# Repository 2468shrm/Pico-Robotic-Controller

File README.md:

# Pico-Robotic-Controller

A carrier board for a Raspberry Pi Pico (W) for use in FRC robotics. Similar
to the XRP board.

## Disclaimer / Warning

This is an experimental device. Not all interfaces have been fully validated
for proper function. Use at your own risk.

## Introduction (Motivation)

You may assume that this board is indended to compete with the XRP product
from WPI, other developers, and SparkFun. __It is not__. The XRP board is
awesome and I'll likely end up acquiring one (or two) for myself. I have
been working on lo w-cost, roboRIO-like carrier boards for FRC for a couple
of years.

Why create a carrier board like the roboRIO? To enable a lower-cost
prototyping solution. This solution makes it less risky to a costly
than using a roboRIO solution. Breaking a roboRIO means costly replacement
that is sometimes hard to replace. One goal was to provide as many
similar interfaces as possible but cost 25% the budget.

Things I didn't need to do with my use model: support LabVIEW despite being
a team who lives and breaths LabVIEW. I did want to support rapid prototyping
and so exploring circuitpython was a goal; particularly because of the
library support for the STEMMA QT/Qwiic based sensors available from
Adafruit.

## Board Images

## Board Features

The carrier board has the following interfaces and features.

- RaspberryPi Pico W board
  - Does the thinking
  - Provides WiFi and/or Bluetooth
  - Socketed for replacemnt if needed
- Adafruit Picobell CAN board (optional)
  - Provides CAN connectivity for integration into FRC robots allowing CAN-connected applications (e.g. smart sensors)
- Adafruit Ethernet Featherwing board (optional)
  - Provides Ethernet connectivity for integration into FRC robots allowing Ethernet connected applications (e.g. smart sensors)
- Power
  - 12V Battery input provides main board supply
    - 5V regulator module, OR
    - A connection to external 5V regulator (using WAGO 250-202) connector if the 5V supply current requirements are higher than the module can provide
  - Servo/PWM interface independently powered by an external source
    - Due to the potential need for different voltage and higher current
    - Not needed if connecting to external motor controllers (REV, CTRE, etc.)
- Four (4) STEMMA QT/Qwiic connections provided through a 4-port I2C switch run off the Pico W I2C 1 interface
- Eight (8) Servo PWM interfaces and an additional 8 PWM signals generated by a 16-channel generator connected to the Pico W I2C 0 interface
 - The Servo PWM interace has its own power input; for increased voltage or current for high-torque servo motors
- Two (2) analog input (ADC) ports, 3V maximum
- Eight (8) digital I/O ports, divided into 2 4-pin groups
  - Uses the roboRIO DIO 3-pin interface
  - Each group provides jumper-selectable power (5V or 3.3V)
  - Pico inputs are 3.3V only (maximum) input, with level shifting based on the group's selected power
  - All DIOs have LEDs to indicate logic level (Dark is LOW, Illuminated is HIGH)
- One NEOPIXEL interface for providing visual sensor status or communication
- One on-board single-pixel NEOPIXEL for board status

## Comparison to XRP Board

The XRP board has some significant philospohical and design choices and features.

- XRP was designed with the intent of learning robotics on a small platform, using the WPILib framework
- Includes four motor controllers (1.5A each) integrated on the PCB
- Has a gyro and accelerometer integrated on the PCB
- The connectors are six-position JST (vertical) that integrates digital I/Os for encoders in addition to the M+ and M- motor signals (i.e. not a sensor standard like Qwiic or STEMMA QT)

The PRC does not include any motor controllers on the board. However, it
does provide a 2x5 pin connector and a dedicated PWM generator (I2C bus 0,
address 0x41). The intent is to provide a board with 4 12V, 3.3 A motor
controllers using a separate/dedicated battery input. Providing the capability
to drive four H-Bridges allows for demonstration chassis (skid steer or
Meccanum). This allows replaceable solutions as well as future upgrades for
higher current. Moreover, the PWM / Servo connections allow for use of
a conventional FRC PWM-controlled motor controller.

The PRC provides four STEMMA QT / Qwiic connectors in lieu of a specific set
of sensors (IMU). This allows out use of different sensors dependent on
the application.

The PRC also has CAN and Ethernet connectivity in addition to the WiFi and
BlueTooth provided by the Pice W board.

Differences between the roboRIO, XPR, and PRC boards.
<table>
  <tr style="background-color:#404040">
    <th>Interface / Feature</th>
    <th>RoboRIO</th>
    <th>XRP</th>
    <th>SHRH's Board</th>
  </tr>
  <tr>
    <td>Processing</td>
    <td>Zinq</td>
    <td>RPi Pico W</td>
    <td>RPi Pico W</td>
  </tr>
  <tr>
    <td>Ethernet</td>
    <td>1 Gb</td>
    <td><code>&#8212;</code></td>
    <td>Via 10/100 Mb FeatherWing</td>
  </tr>
  <tr>
    <td>WiFi</td>
    <td>Via OpenMesh</td>
    <td>Y</td>
    <td>Y</td>
  </tr>
  <tr>
    <td>USB Host</td>
    <td>Y</td>
    <td><code>&#8212;</code></td>
    <td><code>&#8212;</code></td>
  </tr>
  <tr>
    <td>CAN</td>
    <td>Y</td>
    <td><code>&#8212;</code></td>
    <td>Via Picobell CAN board</td>
  </tr>
  <tr>
    <td>Relay</td>
    <td>Y</td>
    <td><code>&#8212;</code></td>
    <td><code>&#8212;</code></td>
  </tr>
  <tr>
    <td>Digital I/O</td>
    <td>10 + MXP</td>
    <td><code>&#8212;</code></td>
    <td>8</td>
  </tr>
  <tr>
    <td>ADC</td>
    <td>4</td>
    <td><code>&#8212;</code></td>
    <td>2</td>
  </tr>
  <tr>
    <td>I2C</td>
    <td>2</td>
    <td><code>&#8212;</code></td>
    <td><code>&#8212;</code></td>
  </tr>
  <tr>
    <td>STEMMA QT / Qwiic</td>
    <td><code>&#8212;</code></td>
    <td>4</td>
    <td>4</td>
  </tr>
  <tr>
    <td>SPI</td>
    <td>2</td>
    <td><code>&#8212;</code></td>
    <td><code>&#8212;</code></td>
  </tr>
  <tr>
    <td>RS-232</td>
    <td>1</td>
    <td><code>&#8212;</code></td>
    <td><code>&#8212;</code></td>
  </tr>
  <tr>
    <td>Gyro</td>
    <td>Y</td>
    <td>6 DOF IMU (LSM6DSO)</td>
    <td><code>&#8212;</code></td>
  </tr>
  <tr>
    <td>Status LEDs</td>
    <td>Y</td>
    <td>Pico W LED</td>
    <td>Y (NEOPIXEL) + Pico W LED</td>
  </tr>
  <tr>
    <td>NEOPIXEL String</td>
    <td>2 via PWM outputs</td>
    <td><code>&#8212;</code></td>
    <td>Y</td>
  </tr>
  <tr>
    <td>Low-Current Motor Control</td>
    <td><code>&#8212;</code></td>
    <td>4</td>
    <td>4 on sidecar board</td>
  </tr>
  <tr>
    <td>Per H-Bridge Max Current</td>
    <td><code>&#8212;</code></td>
    <td>1.5 A</td>
    <td>3.3 A</td>
  </tr>
  <tr>
    <td>I/Os Per Motor Interface</td>
    <td><code>&#8212;</code></td>
    <td>2 (equivalent of STEMMA per motor)</td>
    <td><code>&#8212;</code></td>
  </tr>
  <tr>
    <td>Reset Button</td>
    <td>Y</td>
    <td>Y</td>
    <td>Y</td>
  </tr>
  <tr>
    <td>Power In</td>
    <td>12 V</td>
    <td>5-11 V</td>
    <td>12 V</td>
  </tr>
  <tr>
    <td>Power Conntector</td>
    <td>Sauro</td>
    <td>Barrel</td>
    <td>Wago 250-202</td>
  </tr>
  <tr>
    <td></td>
    <td></td>
    <td></td>
    <td></td>
  </tr>
</table>

Differences between the XRP and PRC pin usage and functions.

<table>
  <tr style="background-color:#404040">
    <th>Pin</th>
    <th>Pico W Alternatives</th>
    <th>XRP Interface</th>
    <th>XRP Function</th>
    <th>PRC Board</th>
  </tr>
  <tr>
    <td>GPIO 0</td>
    <td>U0 TX / SDA0 / MISO0</td>
    <td rowspan="4">Motor 3</td>
    <td>Encoder A</td>
    <td>DIO 0</td>
  </tr>

  <tr>
    <td>GPIO 1 </td>
    <td>U0 RX / SCL0 / CS0</td>
    <td>Encoder B</td>
    <td>DIO 1</td>
  </tr>
  <tr>
    <td>GPIO 2</td>
    <td>SDA1 / SCK0</td>
    <td>Phase</td>
    <td>PWM Gen SDA</td>
  </tr>
  <tr>
    <td>GPIO 3 </td>
    <td>SCL1 / MOSI0</td>
    <td>Enable</td>
    <td>PWM Gen SCL</td>
  </tr>
  <tr>
    <td>GPIO 4 </td>
    <td>U1 TX / SDA0 / MISO0</td>
    <td rowspan="4">Left Motor</td>
    <td>Encoder A</td>
    <td>I2C Switch SDA</td>
  </tr>
  <tr>
    <td>GPIO 5</td>
    <td>U1 RX / SCL0 / CS0</td>
    <td>Encoder B</td>
    <td>I2C Switch SCL</td>
  </tr>
  <tr>
    <td>GPIO 6</td>
    <td>SDA1 / SCK0</td>
    <td>Phase</td>
    <td>DIO 2</td>
  </tr>
  <tr>
    <td>GPIO 7</td>
	<td>SCL1 / MOSI0</td>
    <td>Enable</td>
    <td>DIO 3</td>
  </tr>
  <tr>
    <td>GPIO 8</td>
    <td>U1 TX / SDA0 / MISO1</td>
    <td rowspan="4">Motor 4</td>
    <td>Encoder A</td>
    <td>DIO 4</td>
  </tr>
  <tr>
    <td>GPIO 9</td>
    <td>U1 RX / SCL0 / CS1</td>
    <td>Encoder B</td>
    <td>DIO 5</td>
  </tr>
  <tr>
    <td>GPIO 10</td>
    <td>SDA1 / SCK1</td>
    <td>Phase</td>
    <td>DIO 6</td>
  </tr>
  <tr>
    <td>GPIO 11</td>
 	<td>SCL1 / MOSI1</td>
    <td>Enable</td>
    <td>DIO 7</td>
  </tr>
  <tr>
    <td>GPIO 12</td>
	<td>U0 TX / SDA0 / MISO1</td>
    <td rowspan="4">Right Motor</td>
    <td>Encoder A</td>
    <td>PWM Gen Enable</td>
  </tr>
  <tr>
    <td>GPIO 13</td>
	<td>U0 RX / SCL0 / CS1</td>
    <td>Encoder B</td>
    <td>Reset Switch</td>
  </tr>
  <tr>
    <td>GPIO 14</td>
 	<td>SDA1 / SCK1</td>
    <td>Phase</td>
    <td>not connected</td>
  </tr>
  <tr>
    <td>GPIO 15</td>
    <td>SCL1 / MOSI1</td>
    <td>Enable</td>
    <td>SPI CS (Ethernet)</td>
  </tr>
  <tr>
    <td>GPIO 16</td>
    <td>U0 TX / SDA0 / MISO0</td>
    <td>Servo 1</td>
    <td>Signal</td>
    <td>SPI MISO</td>
  </tr>
  <tr>
    <td>GPIO 17</td>
    <td>U0 RX / SCL0 / CS0</td>
    <td>Servo 2</td>
    <td>Signal</td>
    <td>NEOPIXEL (board)</td>
  </tr>
  <tr>
    <td>GPIO 18</td>
    <td>SDA1 / SCK0</td>
    <td rowspan="2">IMU / Qwiic</td>
    <td>SDA</td>
    <td>SPI SCK</td>
  </tr>
  <tr>
    <td>GPIO 19</td>
    <td>SCL1 / MOSI0</td>
    <td>SCL</td>
    <td>SPI MOSI</td>
  </tr>
  <tr>
    <td>GPIO 20</td>
    <td>SDA0</td>
    <td rowspan="2">Range</td>
    <td>Trigger</td>
    <td>SPI CS (CAN)</td>
  </tr>
  <tr>
    <td>GPIO 21</td>
    <td>SCL0</td>
    <td>Echo</td>
    <td>SPI INT (CAN)</td>
  </tr>
  <tr>
    <td>GPIO 22</td>
    <td></td>
    <td></td>
    <td>User button / extra</td>
    <td>NEOPIXEL (String)</td>
  </tr>
  <tr>
    <td>GPIO 26</td>
    <td>SDA1 / ADC0</td>
    <td rowspan="2">Line Follower</td>
    <td>Left</td>
    <td>ADC 0</td>
  </tr>
  <tr>
    <td>GPIO 27</td>
    <td>SCL1 / ADC1</td>
    <td>Right</td>
    <td>ADC 1</td>
  </tr>
  <tr>
    <td>GPIO 28</td>
    <td></td>
    <td></td>
    <td>VIN_meas / extra</td>
    <td>not connected</td>
  </tr>
</table>

## PRC Board Detail / Theory of Operation

The following describes the PRC board components, features, and 

When exploring the board's detail and function, it may be helpful to refer to
the board's schematic ([Link](https://github.com/2468shrm/Pico-Robotic-Controller/blob/main/Images/Pico%20Robotic%20Controller%20Schematic.pdf)).

### Main Power / Battery Input

The power system has the following components:
- +BATT - The main power supply (+BATT) is connected to J1, a 2-position WAGO 250 series connector. The typical use is a 12V battery or power supply.
- +12V - Connected to +BATT through a diode-capacitor filter. The intent of the filter is to avoid brownouts on the robot from affecting board performance.
- +5V - The Pico W uses a 5V source normally supplied by USB's VBUS. However, the board provides a 5V source. This is done via either installing a 5V 3A regulator module ([Amazon Link](https://www.amazon.com/gp/product/B08JZ5FVLC)), or by installing a 2-position WAGO 250-series connector (J11) and providing an external 5V supply.  The external solution would be used only in situations where 3A is insufficient (e.g. a very long NEOPIXEL strip).
- SERVO_VDD - A dedicated power input is provided for use cases involving servo motors. This is required since the +5V supply is limited to 3A which may not be sufficient for servo motors in stall. Moreover, while servo motors may operate at 5V, they're better at operating at higher voltages (6V).
- VSYS - VSYS is a pin on the Pico W board that is sourced from VBUS through a Schottky diode, but this is only functional when the VBUS is connected.  VSYS is also soured by a PFET (Q1, a DMG2305UX-13) as recommended by the Pico W datasheet ([Raspberry Pi Pico W Datasheet](https://datasheets.raspberrypi.com/picow/pico-w-datasheet.pdf#page=15)). Refer to sections 3.4 and 3.5 of the datasheet for details. This allows a computer connected via VBUS at the same time the board is powred by +BATT (or the J11 external source).
- VBUS - The USB OTG's power pin. Note that J6 is provided (and needs to have a jumper installed)  in order to source VBUS from the board's +5V supply when the USB OTG interface is being used in HOST mode.

### Processing and Communications
The PRC is intended to serve as a low-cost roboRIO.  To that end it includes
computation and communication at the heart of the system.

#### Pi Pico W
The PRC includes a socket to install a Raspberry Pi Pico W board. This
is in component designator U2.

#### CAN  
The PRC includes a socket to install an Adafruit Picowbell board
([link](https://www.adafruit.com/product/5728)). This board uses a Microchip
MCP2515 SPI to CAN device. This is an optional device; the PRC can opeate with
CAN, Ethernet, Both, or none.

The CAN and Ethernet boards share the same SPI MOSI, MISO, and SCK signals, but
have independent chips selects (and in the case of CAN a separate interrupt
signal).

#### Ethernet
The PRC includes a socket to install an Adafruit Ethernet Featherwing
([link](https://www.adafruit.com/product/3201)).This is an optional device;
the PRC can opeate with CAN, Ethernet, Both, or none.

The CAN and Ethernet boards share the same SPI MOSI, MISO, and SCK signals, but
have independent chips selects.

### Sensors
There are multiple digital and analog sensor connection methods used with the PRC
board. These include a number of I2C interfaces that use the Qwiic/STEMMA QT format,
analog inputs, and digital I/Os.

#### Qwiic / STEMMA QT
There are four (4) Qwiic/STEMMA QT connectors. These connectors (X1-X4) connect
to the Pico W I2C bus 1 via an TCA9546 4-port I2C switch/mux (I2C bus 1
address 0x70).

The Qwiic/STEMMA QT connector provide the two I2C signals (each connector coming
from one dedicated output of the I2C mux/switch), 3.3V, and GND. This format
connector assumes the attached device provides the SDA/SCL pull ups and any local
level shifting to the sensor. It also assumes the board provides 3.3V conversion
to the sensor used. Each Qwiic/STEMMA QT connection may chain multiple sensors
provided their I2C addresses do not collide and the signal integrity of the I2C
signals is maintained.

The Qwiic/STEMMA QT to mux/switch channel is provided in the following table.
<table>
  <tr style="background-color:#404040">
    <th>Channel</th>
    <th>Interface</th>
    <th>Function / # </th>
  </tr>
  <tr>
    <td>0</td>
    <td rowspan="2">X1</td>
    <td>SDA0</td>
  </tr>
  <tr>
    <td>1</td>
    <td>SCL0</td>
  </tr>
  <tr>
    <td>2</td>
    <td rowspan="2">X2</td>
    <td>SDA1</td>
  </tr>
  <tr>
    <td>3</td>
    <td>SCL1</td>
  </tr>
  <tr>
    <td>4</td>
    <td rowspan="2">X3</td>
    <td>SDA3</td>
  </tr>
  <tr>
    <td>5</td>
    <td>SCL3</td>
  </tr>
  <tr>
    <td>6</td>
    <td rowspan="2">X4</td>
    <td>SDA2</td>
  </tr>
  <tr>
    <td>7</td>
    <td>SCL2</td>
  </tr>
</table>

#### ADC / Analog Input
There are two (2) analog input pins that connect to the Pico W ADC0 and ADC1
pins. The board buffers the input signals between pin and Pico W ADC inputs with
a unity gain opamp.  This is done to provide the highest accuracy while allowing
the use of sensors with larger output impedances.

The ADCs use a 3x2 pin header, and uses the same pin layout as the roboRIO's AIN
connections; signal, power, and ground. Ground is closest to the board edge and
power in the middle. The power pin voltage is 3.3V since the Pico W ADC range is
0 to 3.3 V.

#### Digital Input/Output (DIO)
There are eight (8) DIOs arranged in two groups of four, DIO0-3 and DIO4-7.
Each group has an independent level shifter (TXS0104E). The level shifter
includes 10 kΩ pull ups. Since the Pico W has 3.3V (only) I/Os, the VCCA of both
level shifters use 3.3 V. However the VCCB of the external side of each level
shifter is set by an external jumper (J5 for DIO0-3 and J9 for DIO4-7) and
can be set to either 3.3 V or 5 V.

Each DIO group uses a 3x4 pin header, and uses the same pin layout as the roboRIO's
DIO connections; signal, power, and ground. Ground is closest to the board edge
and power in the middle. The power pin voltage is the same voltage pdovided
to the VCCB of the level shifter.

### Motor Control
There are two main interfaces for controlling motors and servos.
1. PWM/Servo interface. Eight (8) conventional PWM/Servo connections.
1. There is also a dedicated motor control interface to connect to a custom, 4 channel, low-current, motor driver board.

#### PWM/Servo

The PWM/Servo interface uses the first 8 channels of a PCA9685 PWM generator
(I2C bus 0, I2C address 0x40).

If using the PWM/Servo interface for servo control, connect the J12 connector
(supplying SERVO_VDD) to an external power supply. This is not needed if the
PWM/Servo interface is being used to connect to external motor controllers
from REV, CTRE, etc.

<table>
  <tr style="background-color:#404040">
    <th>Channel</th>
    <th>Interface</th>
    <th>Function / # </th>
  </tr>
  <tr>
    <td>0</td>
    <td rowspan="8">PWM Block</td>
    <td>PWM 0</td>
  </tr>
  <tr>
    <td>1</td>
    <td>PWM 1</td>
  </tr>
  <tr>
    <td>2</td>
    <td>PWM 2</td>
  </tr>
  <tr>
    <td>3</td>
    <td>PWM 3</td>
  </tr>
  <tr>
    <td>4</td>
    <td>PWM 4</td>
  </tr>
  <tr>
    <td>5</td>
    <td>PWM 5</td>
  </tr>
  <tr>
    <td>6</td>
    <td>PWM 6</td>
  </tr>
  <tr>
    <td>7</td>
    <td>PWM 7</td>
  </tr>
  <tr>
    <td>8-15</td>
    <td colspan="2">Unused</td>
  </tr>
</table>

#### Motor Control

The motor control interface uses the first 8 channels of a dedicated PCA9685 PWM
generator (I2C bus 0, I2C address 0x41).

These connect to the motor controller board and drive four (4) instances of a TI
DRV8870 3.5 A motor controller. This board is intended to be used in FTC-class
robots or for classroom and learning (not competition) use. 

The DRV8870 has 2 signal inputs per IC (IN1, IN2).  The motor controller
operates as follows:

<table>
  <tr style="background-color:#404040">
    <th>IN1</th>
    <th>IN2</th>
    <th>OUT 1</th>
    <th>OUT 2</th>
    <th>Motor Action </th>
  </tr>
  <tr>
    <td>0</td>
    <td>0</td>
    <td>High-Z</td>
    <td>High-Z</td>
    <td><u>Coast</u><br />Current direction remains and flows through reverse body diodes of H-bridge. </td>
  </tr>
  <tr>
    <td>0</td>
    <td>1</td>
    <td>GND</td>
    <td>VDD</td>
    <td><u>Reverse</u><br />Current flows from OUT 2 to OUT 1.</td>
  </tr>
  <tr>
    <td>1</td>
    <td>0</td>
    <td>VDD</td>
    <td>GND</td>
    <td><u>Forward</u><br /> Current flows from OUT 1 to OUT 2.</td>
  </tr>
  <tr>
    <td>1</td>
    <td>1</td>
    <td>GND</td>
    <td>GND</td>
    <td><u>Brake</u><br />Current recirculates between low-side H-bridge.</td>
  </tr>
</table>

Note: When pulse width modulating the IN1 & IN2 to provide speed control
of the attached motors, it is important to realize that operating in coast
or brake modes is important to consider.

In coast mode, the motor coasts when both IN1 and IN2 are 0. This matches
the normal signal polarity of a PWM signal (high represents active).

<table>
  <tr style="background-color:#404040">
    <th>Mode</th>
    <th>Direction</th>
    <th>IN1</th>
    <th>IN2</th>
  </tr>
  <tr>
    <td rowspan="2">Coast</td>
    <td>Forward</td>
    <td>PWM'd</td>
    <td>0</td>
  </tr>
  <tr>
    <td>Reverse</td>
    <td>0</td>
    <td>PWM'd</td>
  </tr>
</table>

The PWM will drive the motor fur the duration of the high time of the duty
cycle and coast through the low time.

In brake mode, the motor breaks when both IN1 and IN2 are 1. This is opposite
the normal signal polarity of a PWM signal, so the signal generation needs
to be inverted and the low-time needs to represent the desired fraction of
the output. Also, the PWM'd input signal must be swapped so that the
correct direction is maintained.

<table>
  <tr style="background-color:#404040">
    <th>Mode</th>
    <th>Direction</th>
    <th>IN1</th>
    <th>IN2</th>
  </tr>
  <tr>
    <td rowspan="2">Coast</td>
    <td>Forward</td>
    <td>1</td>
    <td>inverse PWM'd</td>
  </tr>
  <tr>
    <td>Reverse</td>
    <td>Inverse PWM'd</td>
    <td>1</td>
  </tr>
</table>

Also note this is a not the PWM encoding used for servo controls. The PWM
modulation applied to IN1 and IN2 is full duty cycle of the signal's period
(not the first 2 ms of 20 ms signal).

I2C bus 0, address 0x41
<table>
  <tr style="background-color:#404040">
    <th>Channel</th>
    <th>Interface</th>
    <th>Function / # </th>
  </tr>
  <tr>
    <td>0</td>
    <td rowspan="2">M0</td>
    <td>IN1</td>
  </tr>
  <tr>
    <td>1</td>
    <td>IN2</td>
  </tr>
  <tr>
    <td>2</td>
    <td rowspan="2">M1</td>
    <td>IN1</td>
  </tr>
  <tr>
    <td>3</td>
    <td>IN2</td>
  </tr>
  <tr>
    <td>4</td>
    <td rowspan="2">M2</td>
    <td>IN1</td>
  </tr>
  <tr>
    <td>5</td>
    <td>IN2</td>
  </tr>
  <tr>
    <td>6</td>
    <td rowspan="2">M3</td>
    <td>IN1</td>
  </tr>
  <tr>
    <td>7</td>
    <td>IN2</td>
  </tr>
  <tr>
    <td>8-15</td>
    <td colspan="2">Unused</td>
  </tr>
</table>

### Status

The PRC provides simple interfaces for visual status.

#### NEOPIXEL on PCB

A single NEOPIXEL device is mounted on the board. This is intended to provide
visual status while developing code or tuning algodrithms and mechanisms.

#### NEOPIXEL Strip

A 3-position 250-series WAGo connector is provided to connect a NEOPIXEL strip
to the board. This is intended to provide visual status for distant observation.
The most common use case being robot to driver status across the FRC field.

### PCB Layer Usage

The PRC PCB uses four layers primarily to keep power distribution as clean
as possible. The layers are used as described in the following table. Each
layer label includes a link to the layer's image.

<table>
  <tr style="background-color:#404040">
    <th>Layer</th>
    <th>Use</th>
  </tr>
  <tr>
    <td rowspan="3"><a href="https://github.com/2468shrm/Pico-Robotic-Controller/blob/main/Images/F.Cu.png">F.Cu</a></td>
    <td>+3V3 fill (main +3.3V plane)</td>
  </tr>
  <tr>
    <td>Signal routing</td>
  </tr>
  <tr>
    <td>Component placement (SMT)</td>
  </tr>
  <tr>
    <td rowspan="2"><a href="https://github.com/2468shrm/Pico-Robotic-Controller/blob/main/Images/In1.Cu.png">In1.Cu</a></td>
    <td>+BATT fill (main battery plane)</td>
  </tr>
  <tr>
    <td>Signal routing</td>
  </tr>
  <tr>
    <td rowspan="3"><a href="https://github.com/2468shrm/Pico-Robotic-Controller/blob/main/Images/In2.Cu.png">In2.Cu</a></td>
    <td>+5V fill (main +5V plane)</td>
  </tr>
  <tr>
    <td>VIOA and VIOB (DIO power)</td>
  </tr>
  <tr>
    <td>Signal routing (across CPU, CAN, Eth modules)</td>
  </tr>
  <tr>
    <td rowspan="2"><a href="https://github.com/2468shrm/Pico-Robotic-Controller/blob/main/Images/B.Cu.png">B.Cu</a></td>
    <td>Ground fill (main ground plane)</td>
  </tr>
  <tr>
    <td>+5V fill (small fills and 5V traces)</td>
  </tr>
</table>

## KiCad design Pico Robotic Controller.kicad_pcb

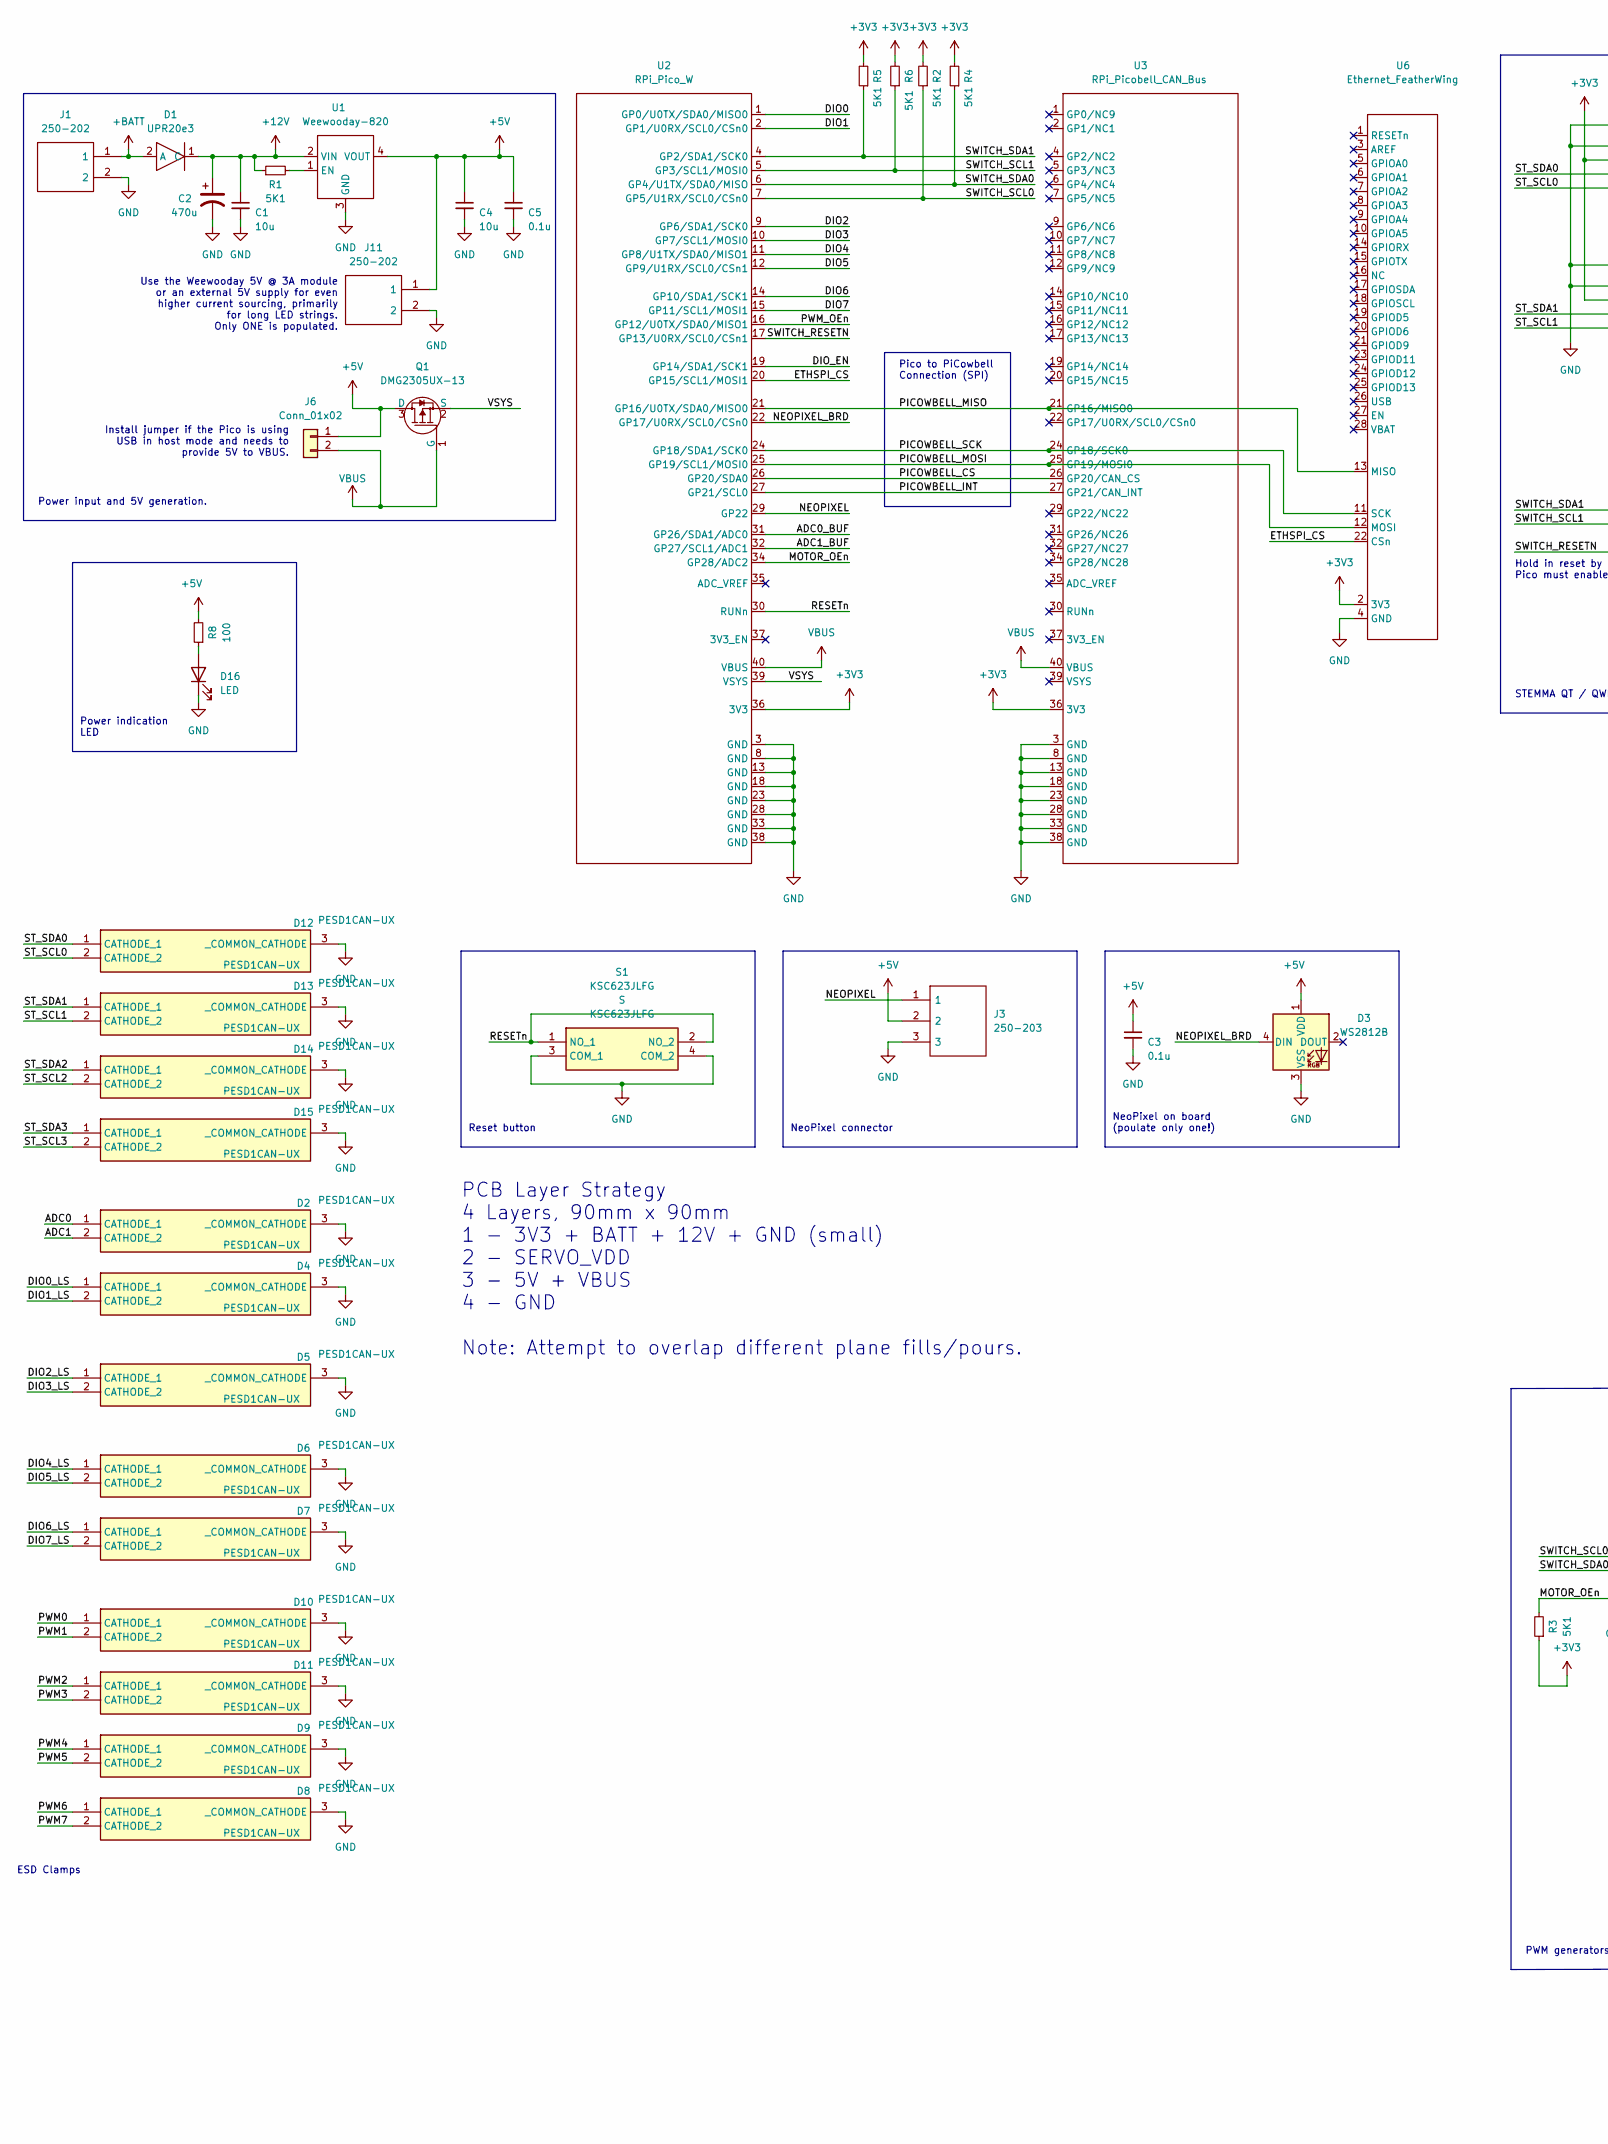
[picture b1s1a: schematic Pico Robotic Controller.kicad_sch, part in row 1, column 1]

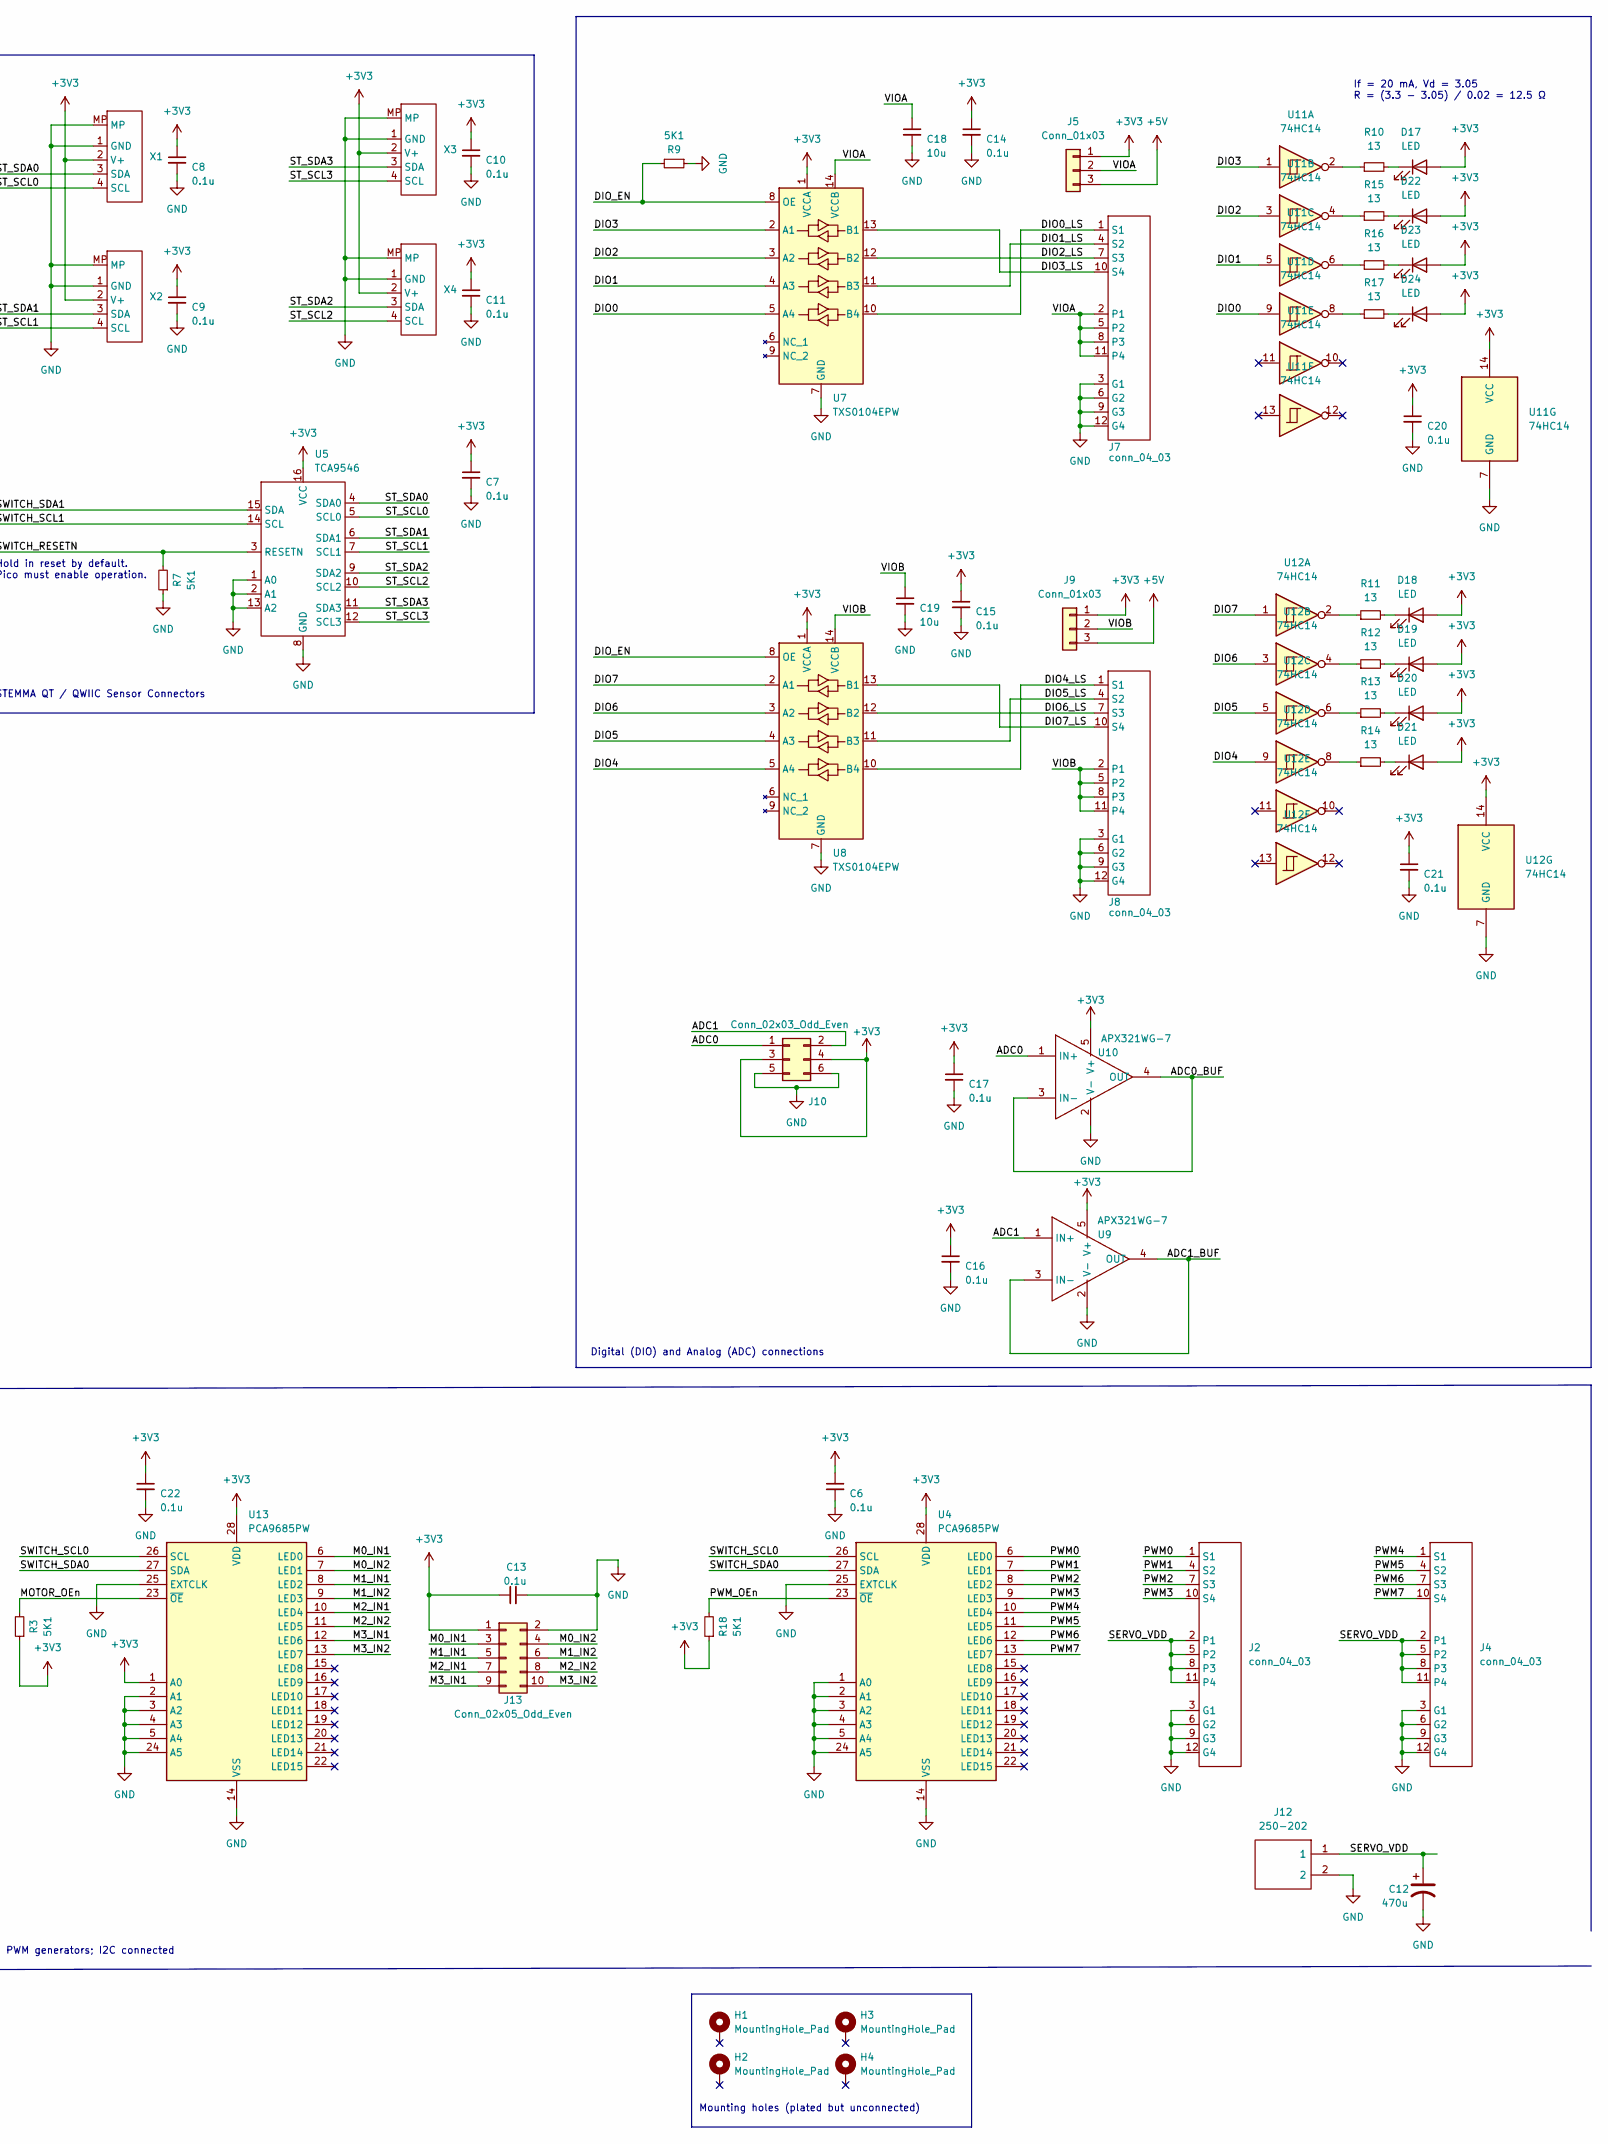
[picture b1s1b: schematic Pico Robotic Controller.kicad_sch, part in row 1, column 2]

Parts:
C1, C4: 10u; C_1206_3216Metric; LCSC C14860
C2, C12: 470u; CAPAE830X1050N; LCSC C340767
C3, C5, C6, C7, C8, C9, C10, C11, C13, C14, C15, C16, C17, C20, C21, C22: 0.1u; C_1206_3216Metric; LCSC C24497
C18, C19: 10u; C_1206_3216Metric; LCSC C24497
D1: UPR20e3; DO-216
D2, D4, D5, D6, D7, D8, D9, D10, D11, D12, D13, D14, D15: PESD1CAN-UX; PESD1CANUX; Mouser Part Number 771-PESD1CANUX
D3: WS2812B; LED_WS2812B_PLCC4_5.0x5.0mm_P3.2mm; LCSC C2761795
D16: LED; LED_1206_3216Metric; LCSC C375581
D17, D18, D19, D20, D21, D22, D23, D24: LED; LED_0603_1608Metric; LCSC C779453
H1, H2, H3, H4: MountingHole_Pad; MountingHole_2.2mm_M2_Pad
J1, J11, J12: 250-202; 250202; Manufacturer_Part_Number 250-202
J2, J4, J7, J8: conn_04_03; conn_04x03
J3: 250-203; 250-203_1; Manufacturer_Part_Number 250-203
J5, J9: Conn_01x03; PinHeader_1x03_P2.54mm_Vertical
J6: Conn_01x02; PinHeader_1x02_P2.54mm_Vertical
J10: Conn_02x03_Odd_Even; PinHeader_2x03_P2.54mm_Vertical
J13: Conn_02x05_Odd_Even; PinHeader_2x05_P2.54mm_Vertical
Q1: DMG2305UX-13; SOT96P240X120-3N; MPN DMG2305UX-13; Digi-Key_PN DMG2305UX-13DICT-ND
R1, R2, R3, R4, R5, R6, R7, R9, R18: 5K1; R_1206_3216Metric; LCSC C118077
R8: 100; R_1206_3216Metric; LCSC C17901
R10, R11, R12, R13, R14, R15, R16, R17: 13; R_0603_1608Metric; LCSC C365384
S1: KSC623JLFG; Mouser Part Number 611-KSC623JLFG
U1: Weewooday-820
U2: RPi_Pico_W; RPi Pico W
U3: RPi_Picobell_CAN_Bus; RPi Pico W
U4, U13: PCA9685PW; TSSOP-28_4.4x9.7mm_P0.65mm; LCSC C2678753
U5: TCA9546; TSSOP-16_4.4x5mm_P0.65mm; LCSC C201653
U6: Ethernet_FeatherWing; Feather_M4_CAN_Express
U7, U8: TXS0104EPW; TSSOP-14_4.4x5mm_P0.65mm; LCSC C44955
U9, U10: APX321WG-7; SOT95P285X145-5N; Manufacturer_Part_Number APX321WG-7; Mouser Part Number 621-APX321WG-7
U11, U12: 74HC14; TSSOP-14_4.4x5mm_P0.65mm; LCSC C2866133
X1, X2, X3, X4: STEMMA_I2C_QT; JST_SH_BM04B-SRSS-TB_1x04-1MP_P1.00mm_Vertical; LCSC C545725

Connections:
+3V3: C6.1, C7.1, C8.1, C9.1, C10.1, C11.1, C13.1, C14.1, C15.1, C16.1, C17.1, C20.1, C21.1, C22.1, D17.2 (A), D18.2 (A), D19.2 (A), D20.2 (A), D21.2 (A), D22.2 (A), D23.2 (A), D24.2 (A), J5.1, J9.1, J10.3, J10.4, J13.1, R2.2, R3.1, R4.2, R5.2, R6.2, R18.1, U2.36 (3V3), U3.36 (3V3), U4.28 (VDD), U5.16 (VCC), U6.2 (3V3), U7.1 (VCCA), U8.1 (VCCA), U9.5 (V+), U10.5 (V+), U11.14 (VCC), U12.14 (VCC), U13.1 (A0), U13.28 (VDD), X1.2 (V+), X2.2 (V+), X3.2 (V+), X4.2 (V+)
+5V: C3.1, C4.1, C5.1, D3.1 (VDD), J3.2, J5.3, J6.1, J9.3, J11.1, Q1.3 (D), R8.2, U1.4 (VOUT)
+12V: C1.1, C2.1, D1.1 (C), R1.1, U1.2 (VIN)
+BATT: D1.2 (A), J1.1
/ADC0: D2.1 (CATHODE_1), J10.1, U10.1 (IN+)
/ADC0_BUF: U2.31 (GP26/SDA1/ADC0), U10.3 (IN-), U10.4 (OUT)
/ADC1: D2.2 (CATHODE_2), J10.2, U9.1 (IN+)
/ADC1_BUF: U2.32 (GP27/SCL1/ADC1), U9.3 (IN-), U9.4 (OUT)
/DIO0: U2.1 (GP0/U0TX/SDA0/MISO0), U7.5 (A4), U11.9
/DIO0_LS: D4.1 (CATHODE_1), J7.1 (S1), U7.10 (B4)
/DIO1: U2.2 (GP1/U0RX/SCL0/CSn0), U7.4 (A3), U11.5
/DIO1_LS: D4.2 (CATHODE_2), J7.4 (S2), U7.11 (B3)
/DIO2: U2.9 (GP6/SDA1/SCK0), U7.3 (A2), U11.3
/DIO2_LS: D5.1 (CATHODE_1), J7.7 (S3), U7.12 (B2)
/DIO3: U2.10 (GP7/SCL1/MOSI0), U7.2 (A1), U11.1
/DIO3_LS: D5.2 (CATHODE_2), J7.10 (S4), U7.13 (B1)
/DIO4: U2.11 (GP8/U1TX/SDA0/MISO1), U8.5 (A4), U12.9
/DIO4_LS: D6.1 (CATHODE_1), J8.1 (S1), U8.10 (B4)
/DIO5: U2.12 (GP9/U1RX/SCL0/CSn1), U8.4 (A3), U12.5
/DIO5_LS: D6.2 (CATHODE_2), J8.4 (S2), U8.11 (B3)
/DIO6: U2.14 (GP10/SDA1/SCK1), U8.3 (A2), U12.3
/DIO6_LS: D7.1 (CATHODE_1), J8.7 (S3), U8.12 (B2)
/DIO7: U2.15 (GP11/SCL1/MOSI1), U8.2 (A1), U12.1
/DIO7_LS: D7.2 (CATHODE_2), J8.10 (S4), U8.13 (B1)
/DIO_EN: R9.2, U2.19 (GP14/SDA1/SCK1), U7.8 (OE), U8.8 (OE)
/ETHSPI_CS: U2.20 (GP15/SCL1/MOSI1), U6.22 (CSn)
/M0_IN1: J13.3, U13.6 (LED0)
/M0_IN2: J13.4, U13.7 (LED1)
/M1_IN1: J13.5, U13.8 (LED2)
/M1_IN2: J13.6, U13.9 (LED3)
/M2_IN1: J13.7, U13.10 (LED4)
/M2_IN2: J13.8, U13.11 (LED5)
/M3_IN1: J13.9, U13.12 (LED6)
/M3_IN2: J13.10, U13.13 (LED7)
/MOTOR_OEn: R3.2, U2.34 (GP28/ADC2), U13.23 (~OE)
/NEOPIXEL: J3.1, U2.29 (GP22)
/NEOPIXEL_BRD: D3.4 (DIN), U2.22 (GP17/U0RX/SCL0/CSn0)
/PICOWBELL_CS: U2.26 (GP20/SDA0), U3.26 (GP20/CAN_CS)
/PICOWBELL_INT: U2.27 (GP21/SCL0), U3.27 (GP21/CAN_INT)
/PICOWBELL_MISO: U2.21 (GP16/U0TX/SDA0/MISO0), U3.21 (GP16/MISO0), U6.13 (MISO)
/PICOWBELL_MOSI: U2.25 (GP19/SCL1/MOSI0), U3.25 (GP19/MOSI0), U6.12 (MOSI)
/PICOWBELL_SCK: U2.24 (GP18/SDA1/SCK0), U3.24 (GP18/SCK0), U6.11 (SCK)
/PWM0: D10.1 (CATHODE_1), J2.1 (S1), U4.6 (LED0)
/PWM1: D10.2 (CATHODE_2), J2.4 (S2), U4.7 (LED1)
/PWM2: D11.1 (CATHODE_1), J2.7 (S3), U4.8 (LED2)
/PWM3: D11.2 (CATHODE_2), J2.10 (S4), U4.9 (LED3)
/PWM4: D9.1 (CATHODE_1), J4.1 (S1), U4.10 (LED4)
/PWM5: D9.2 (CATHODE_2), J4.4 (S2), U4.11 (LED5)
/PWM6: D8.1 (CATHODE_1), J4.7 (S3), U4.12 (LED6)
/PWM7: D8.2 (CATHODE_2), J4.10 (S4), U4.13 (LED7)
/PWM_OEn: R18.2, U2.16 (GP12/U0TX/SDA0/MISO1), U4.23 (~OE)
/RESETn: S1.1 (NO_1), S1.2 (NO_2), U2.30 (RUNn)
/SERVO_VDD: C12.1, J2.2 (P1), J2.5 (P2), J2.8 (P3), J2.11 (P4), J4.2 (P1), J4.5 (P2), J4.8 (P3), J4.11 (P4), J12.1
/ST_SCL0: D12.2 (CATHODE_2), U5.5 (SCL0), X1.4 (SCL)
/ST_SCL1: D13.2 (CATHODE_2), U5.7 (SCL1), X2.4 (SCL)
/ST_SCL2: D14.2 (CATHODE_2), U5.10 (SCL2), X4.4 (SCL)
/ST_SCL3: D15.2 (CATHODE_2), U5.12 (SCL3), X3.4 (SCL)
/ST_SDA0: D12.1 (CATHODE_1), U5.4 (SDA0), X1.3 (SDA)
/ST_SDA1: D13.1 (CATHODE_1), U5.6 (SDA1), X2.3 (SDA)
/ST_SDA2: D14.1 (CATHODE_1), U5.9 (SDA2), X4.3 (SDA)
/ST_SDA3: D15.1 (CATHODE_1), U5.11 (SDA3), X3.3 (SDA)
/SWITCH_RESETN: R7.2, U2.17 (GP13/U0RX/SCL0/CSn1), U5.3 (RESETN)
/SWITCH_SCL0: R2.1, U2.7 (GP5/U1RX/SCL0/CSn0), U4.26 (SCL), U13.26 (SCL)
/SWITCH_SCL1: R6.1, U2.5 (GP3/SCL1/MOSI0), U5.14 (SCL)
/SWITCH_SDA0: R4.1, U2.6 (GP4/U1TX/SDA0/MISO), U4.27 (SDA), U13.27 (SDA)
/SWITCH_SDA1: R5.1, U2.4 (GP2/SDA1/SCK0), U5.15 (SDA)
/VIOA: C18.1, J5.2, J7.2 (P1), J7.5 (P2), J7.8 (P3), J7.11 (P4), U7.14 (VCCB)
/VIOB: C19.1, J8.2 (P1), J8.5 (P2), J8.8 (P3), J8.11 (P4), J9.2, U8.14 (VCCB)
/VSYS: Q1.2 (S), U2.39 (VSYS)
GND: C1.2, C2.2, C3.2, C4.2, C5.2, C6.2, C7.2, C8.2, C9.2, C10.2, C11.2, C12.2, C13.2, C14.2, C15.2, C16.2, C17.2, C18.2, C19.2, C20.2, C21.2, C22.2, D2.3 (_COMMON_CATHODE), D3.3 (VSS), D4.3 (_COMMON_CATHODE), D5.3 (_COMMON_CATHODE), D6.3 (_COMMON_CATHODE), D7.3 (_COMMON_CATHODE), D8.3 (_COMMON_CATHODE), D9.3 (_COMMON_CATHODE), D10.3 (_COMMON_CATHODE), D11.3 (_COMMON_CATHODE), D12.3 (_COMMON_CATHODE), D13.3 (_COMMON_CATHODE), D14.3 (_COMMON_CATHODE), D15.3 (_COMMON_CATHODE), D16.1 (K), J1.2, J2.3 (G1), J2.6 (G2), J2.9 (G3), J2.12 (G4), J3.3, J4.3 (G1), J4.6 (G2), J4.9 (G3), J4.12 (G4), J7.3 (G1), J7.6 (G2), J7.9 (G3), J7.12 (G4), J8.3 (G1), J8.6 (G2), J8.9 (G3), J8.12 (G4), J10.5, J10.6, J11.2, J12.2, J13.2, R7.1, R9.1, S1.3 (COM_1), S1.4 (COM_2), U1.3 (GND), U2.3 (GND), U2.8 (GND), U2.13 (GND), U2.18 (GND), U2.23 (GND), U2.28 (GND), U2.33 (GND), U2.38 (GND), U3.3 (GND), U3.8 (GND), U3.13 (GND), U3.18 (GND), U3.23 (GND), U3.28 (GND), U3.33 (GND), U3.38 (GND), U4.1 (A0), U4.2 (A1), U4.3 (A2), U4.4 (A3), U4.5 (A4), U4.14 (VSS), U4.24 (A5), U4.25 (EXTCLK), U5.1 (A0), U5.2 (A1), U5.8 (GND), U5.13 (A2), U6.4 (GND), U7.7 (GND), U8.7 (GND), U9.2 (V-), U10.2 (V-), U11.7 (GND), U12.7 (GND), U13.2 (A1), U13.3 (A2), U13.4 (A3), U13.5 (A4), U13.14 (VSS), U13.24 (A5), U13.25 (EXTCLK), X1.1 (GND), X1.MP, X2.1 (GND), X2.MP, X3.1 (GND), X3.MP, X4.1 (GND), X4.MP
unnamed: D16.2 (A), R8.1
unnamed: D17.1 (K), R10.2
unnamed: D18.1 (K), R11.2
unnamed: D19.1 (K), R12.2
unnamed: D20.1 (K), R13.2
unnamed: D21.1 (K), R14.2
unnamed: D22.1 (K), R15.2
unnamed: D23.1 (K), R16.2
unnamed: D24.1 (K), R17.2
unnamed: R1.2, U1.1 (EN)
unnamed: R10.1, U11.2
unnamed: R11.1, U12.2
unnamed: R12.1, U12.4
unnamed: R13.1, U12.6
unnamed: R14.1, U12.8
unnamed: R15.1, U11.4
unnamed: R16.1, U11.6
unnamed: R17.1, U11.8
VBUS: J6.2, Q1.1 (G), U2.40 (VBUS), U3.40 (VBUS)

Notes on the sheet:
Power input and 5V generation.
Reset button
Use the Weewooday 5V @ 3A module or an external 5V supply for even higher current sourcing, primarily for long LED strings. Only ONE is populated.
Pico to PiCowbell Connection (SPI)
Hold in reset by default. Pico must enable operation.
Power indication LED
NeoPixel on board (poulate only one!)
Install jumper if the Pico is using USB in host mode and needs to provide 5V to VBUS.
If = 20 mA, Vd = 3.05 R = (3.3 - 3.05) / 0.02 = 12.5 Ω
Digital (DIO) and Analog (ADC) connections
NeoPixel connector
STEMMA QT / QWIIC Sensor Connectors
Mounting holes (plated but unconnected)
ESD Clamps
PWM generators; I2C connected
PCB Layer Strategy 4 Layers, 90mm x 90mm 1 - 3V3 + BATT + 12V + GND (small) 2 - SERVO_VDD 3 - 5V + VBUS 4 - GND Note: Attempt to overlap different plane fills/pours.

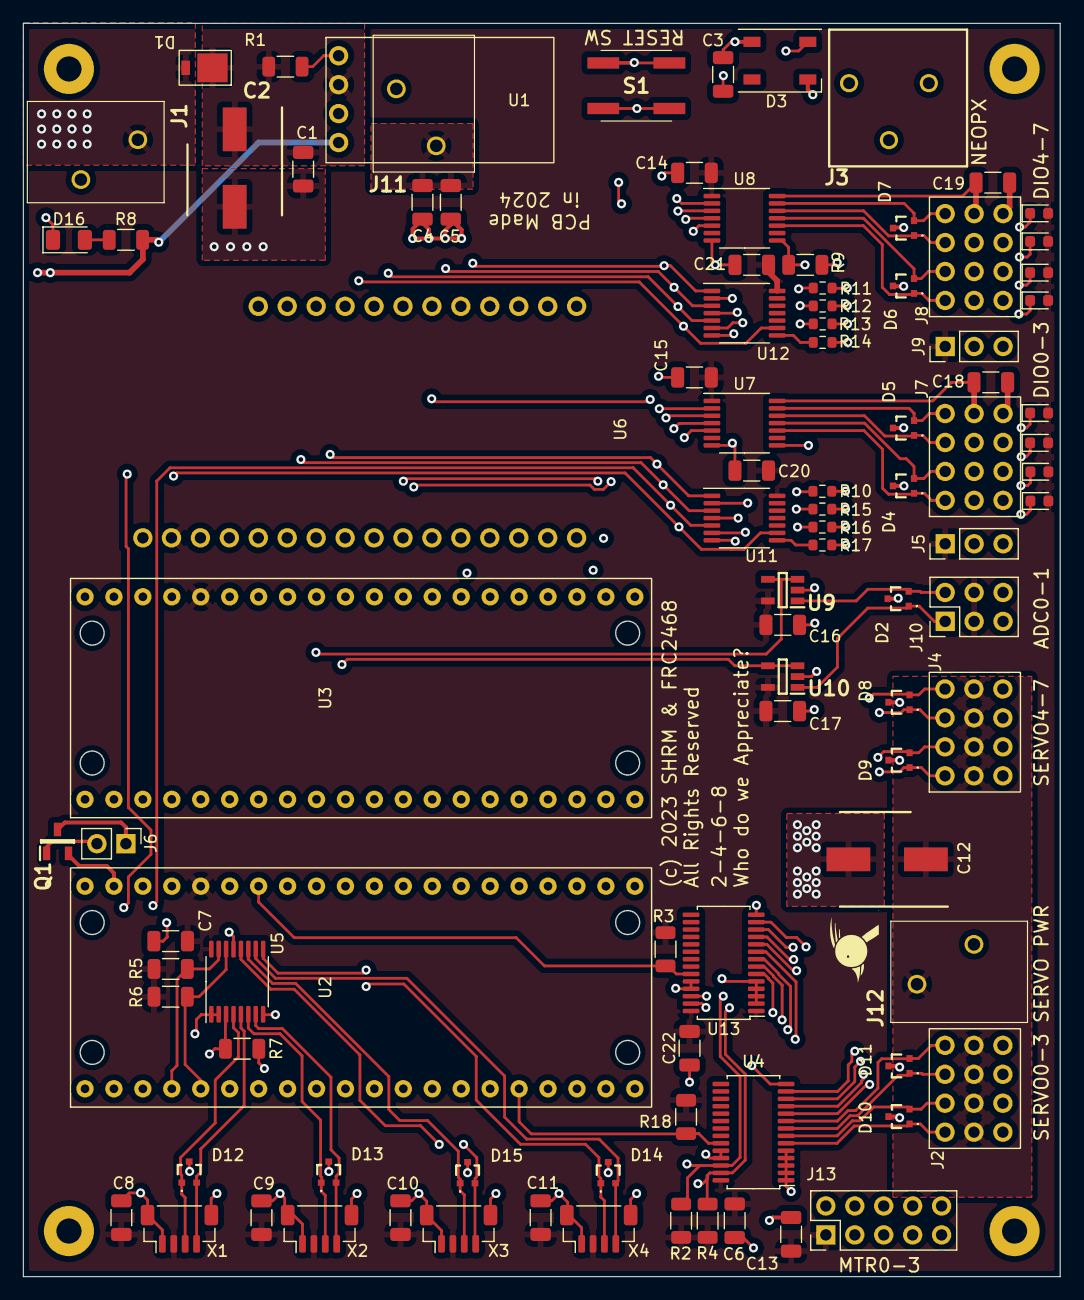
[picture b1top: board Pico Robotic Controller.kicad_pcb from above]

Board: 4 copper layers, 91.0 x 110.0 mm, 100 parts (0 on the bottom side), 89 nets.

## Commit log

2023-12-28 Checkin of board files
2023-12-28 More detail for documentation, but not complete
2023-12-29 adds PCB layer images
2023-12-29 adds schematic PDF
2023-12-30 updated the build files
2023-12-30 updated design files that correct a silkscreen comment (2023 to 2024)
2023-12-30 Updated docs to include a theory of operation
2023-12-30 removing some backups not necessary
2023-12-30 more doc updates, expect more
2023-12-30 yet more doc updates
2023-12-31 updated docs (again)
2023-12-31 updated LED resistor value (13 ohms)
2024-01-03 added disclaimer to docs
2024-01-05 updated 3D images
2024-01-05 updating layer images
2024-01-05 updated KiCAD design files to add separate OEn for motor PWM generator
2024-01-05 updating manufacturing files (Gerbers)
2024-01-07 updated the PWM generator enables to be pull ups from pull down
2024-01-07 updated manufacturing files to match the change in pull ups

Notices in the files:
Pico Robotic Controller.kicad_pcb:
(c) 2023 SHRM & FRC2468
All Rights Reserved
